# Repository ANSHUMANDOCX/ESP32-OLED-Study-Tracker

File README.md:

# ESP32-OLED-Study-Tracker
Its a Compact Server based study tracker using a OLED display and a ESP32 that help one track their study/work time on particular subjects and also lets use set a target using the interactive web page hosted on the ESP

# Parts used 
- Esp32 Wroom
- 2.42 inch OLED Display
- PCB with onboard programmer

# Features
The system uses Display to set timer and keep track of your productive hours. It also has a webpage hosted on the esp that helps u check on the hours spend at a glance. Also one can set target for the day how much time one needs to be productive for.
It also has a Log system thats logs the time we have spent on something and helps us keep track of how productive one has been. It also has a option to download the log all together as a csv file.

# Images 

# BOM
|Part|Supplier|Cost|LINK|
|----|--------|----|----|
|OlED Display|Electronics Comp|$18.9|https://www.electronicscomp.com/waveshare-242inch-oled-display-modulec-12864-resolution-spi-i2c-communication-yellow-display|
|ESP32 WROOM|Electronicscomp|$4.8|https://www.electronicscomp.com/espressif-esp32-wroom-32-16m-128mbit-flash-wifi-bluetooth-module|
|PCB|JLCPCB|$8.64||
|total||$32.5||

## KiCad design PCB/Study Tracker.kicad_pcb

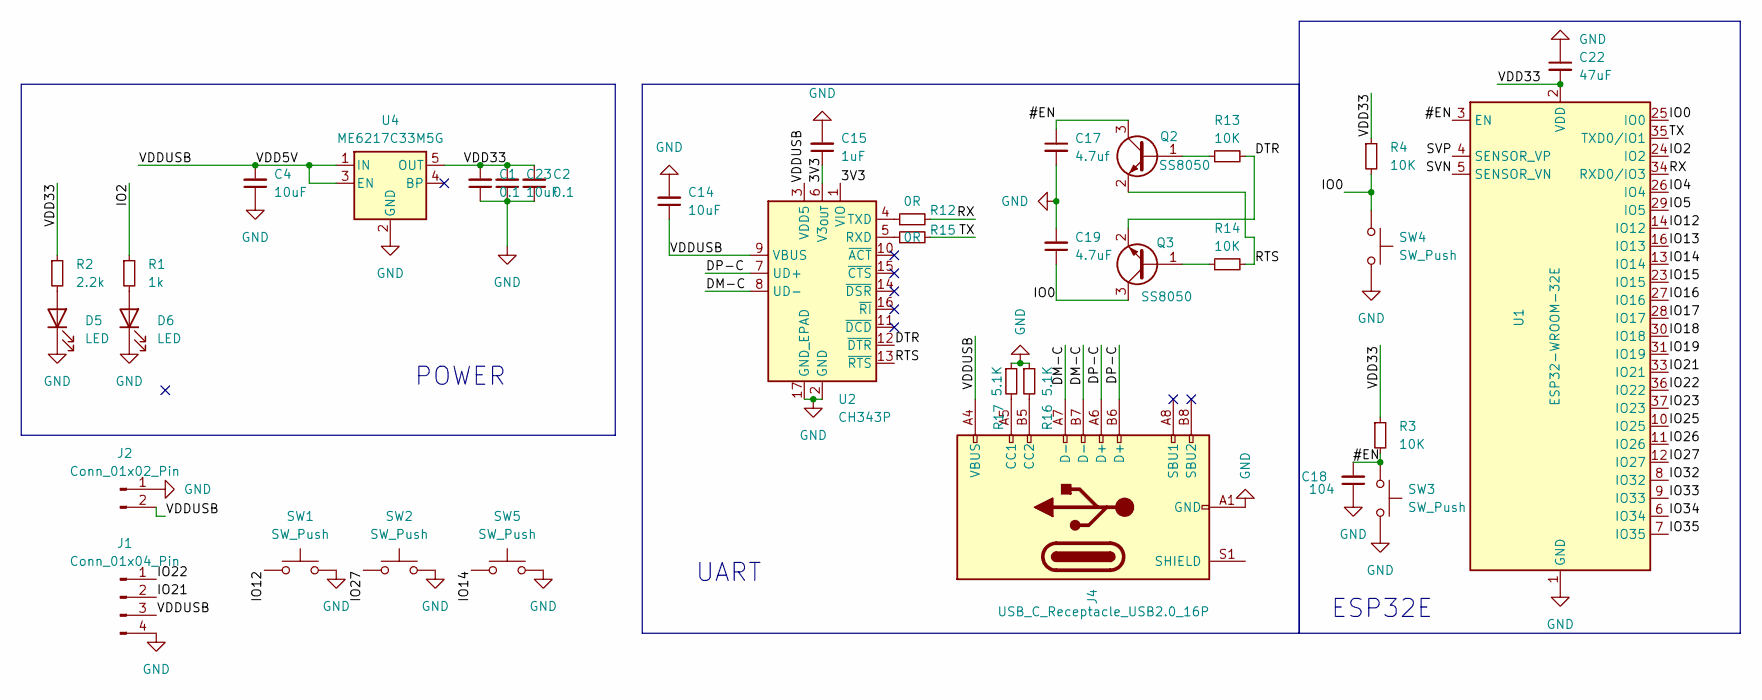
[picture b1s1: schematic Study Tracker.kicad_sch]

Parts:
C1, C2: 0.1; C_0603_1608Metric_Pad1.08x0.95mm_HandSolder
C4, C14, C23: 10uF; C_0603_1608Metric_Pad1.08x0.95mm_HandSolder
C15: 1uF; C_0603_1608Metric_Pad1.08x0.95mm_HandSolder
C17: 4.7uf; C_0603_1608Metric_Pad1.08x0.95mm_HandSolder
C18: 104; C_0603_1608Metric_Pad1.08x0.95mm_HandSolder
C19: 4.7uF; C_0603_1608Metric_Pad1.08x0.95mm_HandSolder
C22: 47uF; C_0603_1608Metric_Pad1.08x0.95mm_HandSolder
D5, D6: LED; LED_0805_2012Metric_Pad1.15x1.40mm_HandSolder
J1: Conn_01x04_Pin; PinHeader_1x04_P2.54mm_Vertical
J2: Conn_01x02_Pin; PinHeader_1x02_P2.54mm_Vertical
J4: USB_C_Receptacle_USB2.0_16P; USB_C_Receptacle_XKB_U262-16XN-4BVC11
Q2, Q3: SS8050; SOT-23
R1: 1k; R_0603_1608Metric_Pad0.98x0.95mm_HandSolder
R2: 2.2k; R_0603_1608Metric_Pad0.98x0.95mm_HandSolder
R3, R4, R13, R14: 10K; R_0603_1608Metric_Pad0.98x0.95mm_HandSolder
R12, R15: 0R; R_0603_1608Metric_Pad0.98x0.95mm_HandSolder
R16, R17: 5.1K; R_0603_1608Metric_Pad0.98x0.95mm_HandSolder
SW1, SW2, SW5: SW_Push; SW_SPST_CK_RS282G05A3
SW3, SW4: SW_Push; SW_Push_SPST_NO_Alps_SKRK
U1: ESP32-WROOM-32E; ESP32-WROOM-32D
U2: CH343P; WCH_QFN-16-1EP_3x3mm_P0.5mm_EP1.8x1.8mm
U4: ME6217C33M5G; SOT-23-5

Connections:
/3V3: C15.1, U2.1 (VIO), U2.6 (V3_{OUT})
/#EN: C17.1, C18.2, Q2.3 (C), R3.2, SW3.1, U1.3 (EN)
/DM-C: J4.A7 (D-), J4.B7 (D-), U2.8 (UD-)
/DP-C: J4.A6 (D+), J4.B6 (D+), U2.7 (UD+)
/DTR: Q3.2 (E), R13.2, U2.12 (~DTR)
/IO0: C19.1, Q3.3 (C), R4.2, SW4.1, U1.25 (IO0)
/IO2: R1.1, U1.24 (IO2)
/IO4: U1.26 (IO4)
/IO5: U1.29 (IO5)
/IO12: SW1.1, U1.14 (IO12)
/IO13: U1.16 (IO13)
/IO14: SW5.1, U1.13 (IO14)
/IO15: U1.23 (IO15)
/IO16: U1.27 (IO16)
/IO17: U1.28 (IO17)
/IO18: U1.30 (IO18)
/IO19: U1.31 (IO19)
/IO21: J1.2, U1.33 (IO21)
/IO22: J1.1, U1.36 (IO22)
/IO23: U1.37 (IO23)
/IO25: U1.10 (IO25)
/IO26: U1.11 (IO26)
/IO27: SW2.1, U1.12 (IO27)
/IO32: U1.8 (IO32)
/IO33: U1.9 (IO33)
/IO34: U1.6 (IO34)
/IO35: U1.7 (IO35)
/RTS: Q2.2 (E), R14.2, U2.13 (~RTS)
/RX: R12.2, U1.34 (RXD0/IO3)
/SVN: U1.5 (SENSOR_VN)
/SVP: U1.4 (SENSOR_VP)
/TX: R15.2, U1.35 (TXD0/IO1)
/VDD5V: C4.2, C14.1, J1.3, J2.2, J4.A4 (VBUS), J4.A9 (VBUS), J4.B4 (VBUS), J4.B9 (VBUS), U2.3 (VDD5), U2.9 (VBUS), U4.1 (IN), U4.3 (EN)
/VDD33: C1.2, C2.2, C22.2, C23.2, R2.1, R3.1, R4.1, U1.2 (VDD), U4.5 (OUT)
GND: C1.1, C2.1, C4.1, C14.2, C15.2, C17.2, C18.1, C19.2, C22.1, C23.1, D5.1 (K), D6.1 (K), J1.4, J2.1, J4.A1 (GND), J4.A12 (GND), J4.B1 (GND), J4.B12 (GND), R16.1, R17.1, SW1.2, SW2.2, SW3.2, SW4.2, SW5.2, U1.1 (GND), U1.15 (GND), U1.38 (GND), U1.39 (GND), U2.2 (GND), U2.17 (GND_EPAD), U4.2 (GND)
unnamed: D5.2 (A), R2.2
unnamed: D6.2 (A), R1.2
unnamed: J4.A5 (CC1), R17.2
unnamed: J4.B5 (CC2), R16.2
unnamed: Q2.1 (B), R13.1
unnamed: Q3.1 (B), R14.1
unnamed: R15.1, U2.5 (RXD)
unnamed: R12.1, U2.4 (TXD)

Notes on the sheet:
UART
POWER
ESP32E

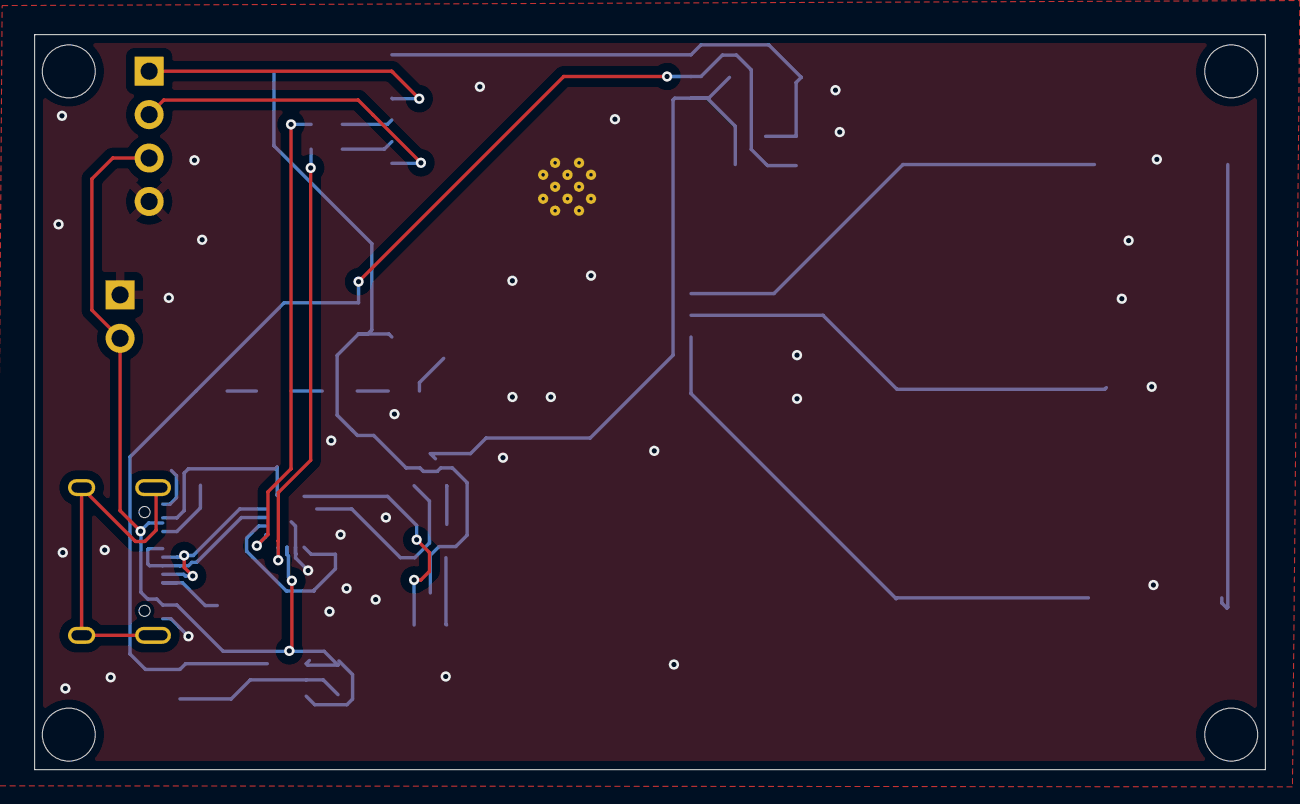
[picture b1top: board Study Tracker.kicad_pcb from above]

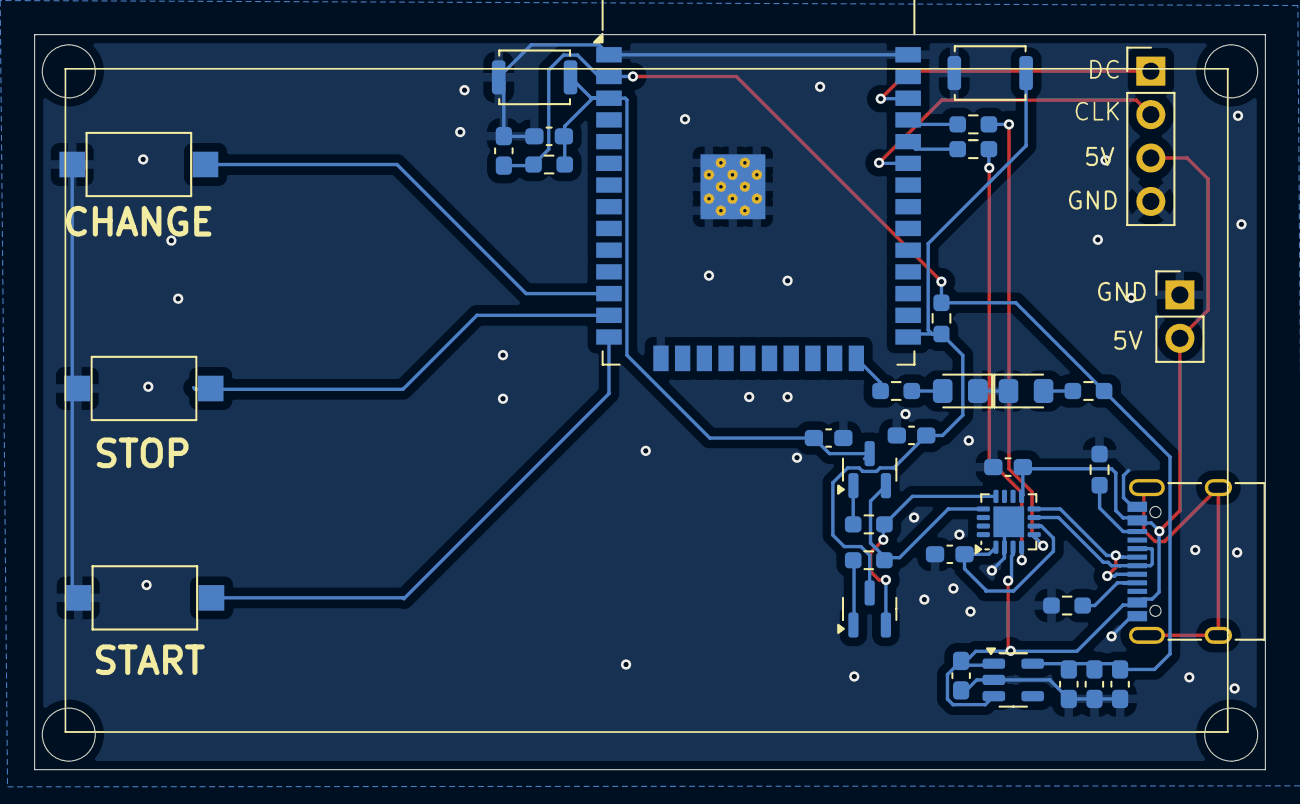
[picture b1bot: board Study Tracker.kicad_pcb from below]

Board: 2 copper layers, 72.0 x 43.0 mm, 35 parts (35 on the bottom side), 26 nets.

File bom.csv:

Designator,Footprint,Quantity,Value,LCSC Part #
"C1, C2",0603,2,0.1,
"C14, C23, C4",0603,3,10uF,
C15,0603,1,1uF,
"C17, C19",0603,2,4.7uf,
C18,0603,1,104,
C22,0603,1,47uF,
"D5, D6",0805,2,LED,
J1,PinHeader_1x04_P2.54mm_Vertical,1,Conn_01x04_Pin,
J2,PinHeader_1x02_P2.54mm_Vertical,1,Conn_01x02_Pin,
J4,USB_C_Receptacle_XKB_U262-16XN-4BVC11,1,USB_C_Receptacle_USB2.0_16P,
"Q2, Q3",SOT-23,2,SS8050,
R1,0603,1,1k,
"R12, R15",0603,2,0R,
"R13, R14, R3, R4",0603,4,10K,
"R16, R17",0603,2,5.1K,
R2,0603,1,2.2k,
"SW1, SW2, SW5",SW_SPST_CK_RS282G05A3,3,SW_Push,
"SW3, SW4",SW_Push_SPST_NO_Alps_SKRK,2,SW_Push,
U1,ESP32-WROOM-32D,1,ESP32-WROOM-32E,
U2,WCH_QFN-16-1EP_3x3mm_P0.5mm_EP1.8x1.8mm,1,CH343P,
U4,SOT-23-5,1,ME6217C33M5G,

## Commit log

2025-10-23 Update README with parts, features, and images
    Added details about parts used, features, and images.
